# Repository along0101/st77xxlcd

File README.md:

# st77xxlcd

st77xxlcd connector

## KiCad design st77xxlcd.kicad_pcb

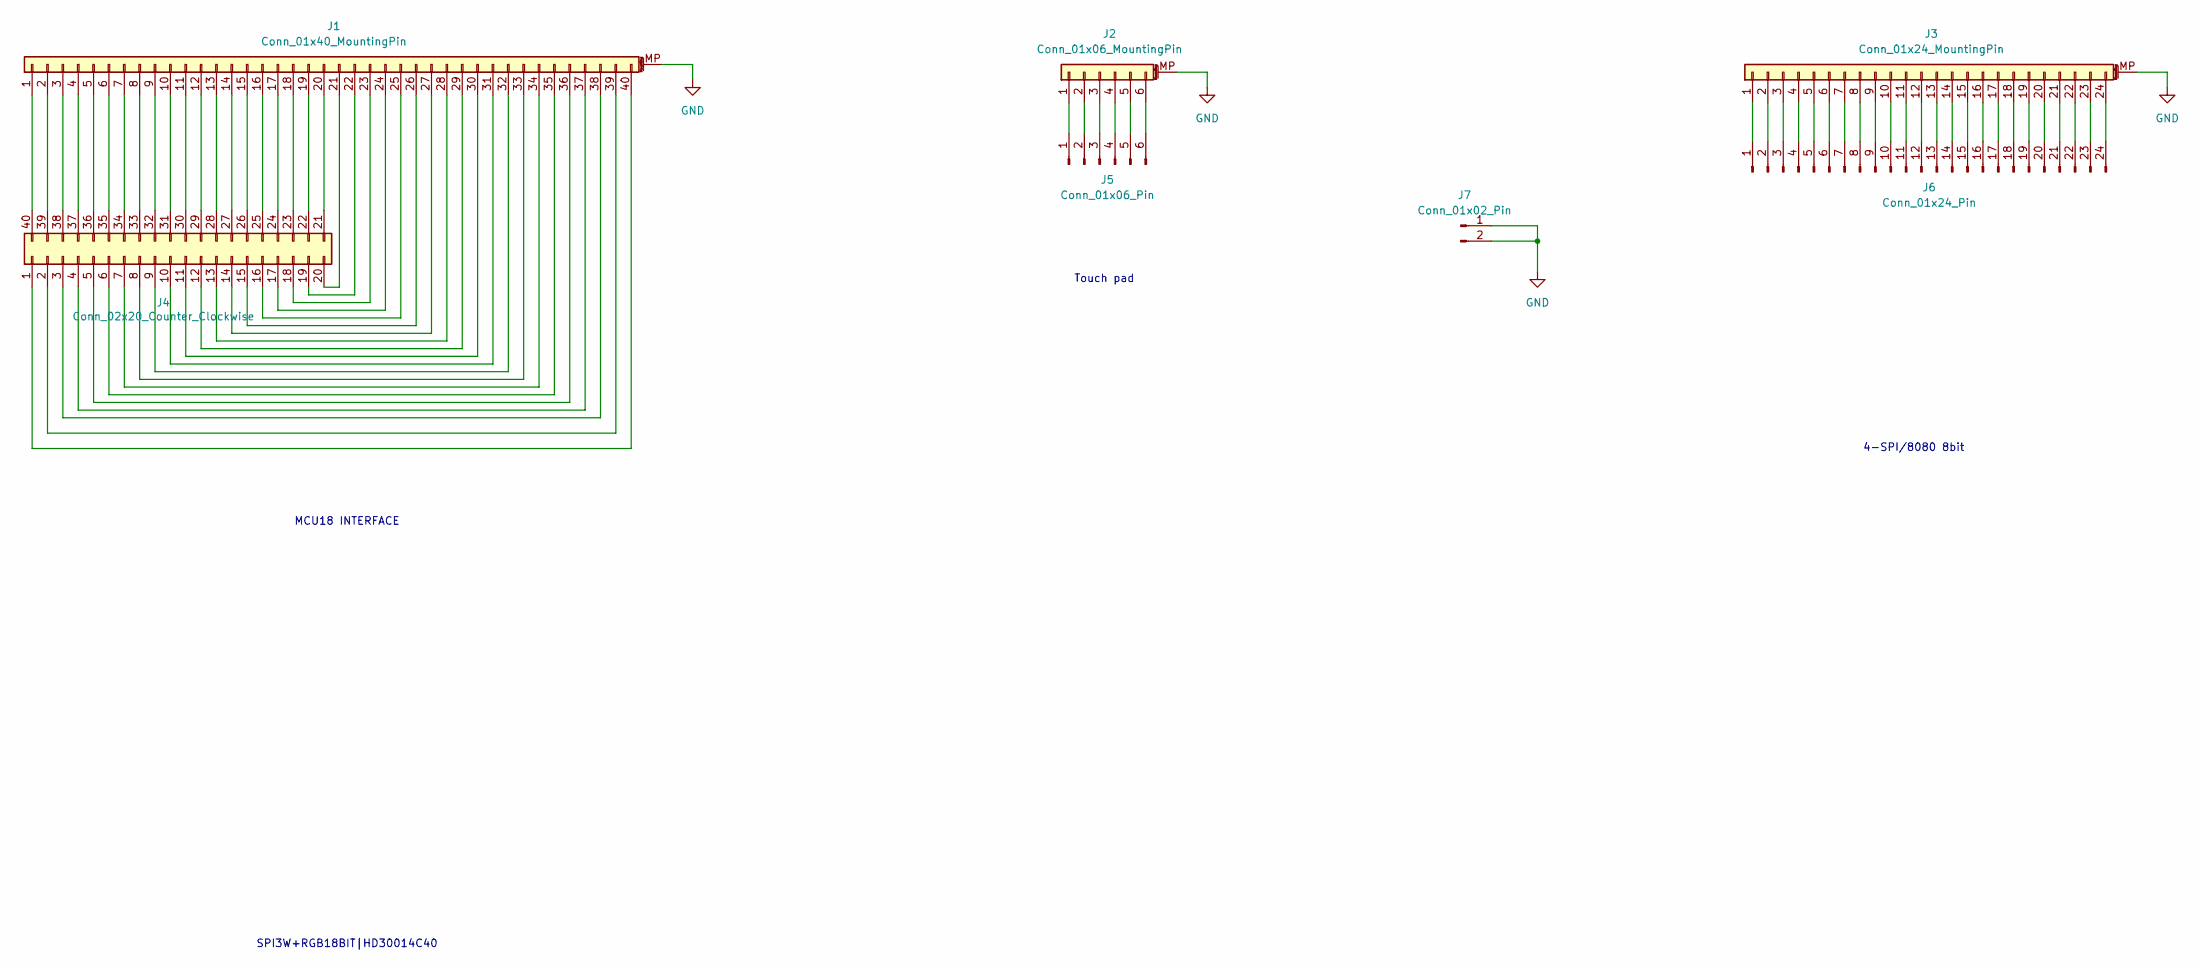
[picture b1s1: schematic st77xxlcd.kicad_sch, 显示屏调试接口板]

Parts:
J1: Conn_01x40_MountingPin; Hirose_FH12-40S-0.5SH_1x40-1MP_P0.50mm_Horizontal
J2: Conn_01x06_MountingPin; Hirose_FH12-6S-0.5SH_1x06-1MP_P0.50mm_Horizontal
J3: Conn_01x24_MountingPin; Hirose_FH12-24S-0.5SH_1x24-1MP_P0.50mm_Horizontal
J4: Conn_02x20_Counter_Clockwise; PinHeader_2x20_P2.54mm_Vertical
J5: Conn_01x06_Pin; PinHeader_1x06_P2.54mm_Vertical
J6: Conn_01x24_Pin; PinHeader_1x24_P2.54mm_Vertical
J7: Conn_01x02_Pin; PinHeader_1x02_P2.54mm_Vertical

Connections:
GND: J1.MP (MountPin), J2.MP (MountPin), J3.MP (MountPin), J7.1, J7.2
unnamed: J1.1, J4.40
unnamed: J1.2, J4.39
unnamed: J1.3, J4.38
unnamed: J1.4, J4.37
unnamed: J1.5, J4.36
unnamed: J1.6, J4.35
unnamed: J1.7, J4.34
unnamed: J1.8, J4.33
unnamed: J1.9, J4.32
unnamed: J1.10, J4.31
unnamed: J1.11, J4.30
unnamed: J1.12, J4.29
unnamed: J1.13, J4.28
unnamed: J1.14, J4.27
unnamed: J1.15, J4.26
unnamed: J1.16, J4.25
unnamed: J1.17, J4.24
unnamed: J1.18, J4.23
unnamed: J1.19, J4.22
unnamed: J1.20, J4.21
unnamed: J1.21, J4.20
unnamed: J1.22, J4.19
unnamed: J1.23, J4.18
unnamed: J1.24, J4.17
unnamed: J1.25, J4.16
unnamed: J1.26, J4.15
unnamed: J1.27, J4.14
unnamed: J1.28, J4.13
unnamed: J1.29, J4.12
unnamed: J1.30, J4.11
unnamed: J1.31, J4.10
unnamed: J1.32, J4.9
unnamed: J1.33, J4.8
unnamed: J1.34, J4.7
unnamed: J1.35, J4.6
unnamed: J1.36, J4.5
unnamed: J1.37, J4.4
unnamed: J1.38, J4.3
unnamed: J1.39, J4.2
unnamed: J1.40, J4.1
unnamed: J2.1, J5.1
unnamed: J2.2, J5.2
unnamed: J2.3, J5.3
unnamed: J2.4, J5.4
unnamed: J2.5, J5.5
unnamed: J2.6, J5.6
unnamed: J3.1, J6.1
unnamed: J3.2, J6.2
unnamed: J3.3, J6.3
unnamed: J3.4, J6.4
unnamed: J3.5, J6.5
unnamed: J3.6, J6.6
unnamed: J3.7, J6.7
unnamed: J3.8, J6.8
unnamed: J3.9, J6.9
unnamed: J3.10, J6.10
unnamed: J3.11, J6.11
unnamed: J3.12, J6.12
unnamed: J3.13, J6.13
unnamed: J3.14, J6.14
unnamed: J3.15, J6.15
unnamed: J3.16, J6.16
unnamed: J3.17, J6.17
unnamed: J3.18, J6.18
unnamed: J3.19, J6.19
unnamed: J3.20, J6.20
unnamed: J3.21, J6.21
unnamed: J3.22, J6.22
unnamed: J3.23, J6.23
unnamed: J3.24, J6.24

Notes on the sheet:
4-SPI/8080 8bit
MCU18 INTERFACE
SPI3W+RGB18BIT|HD30014C40
Touch pad

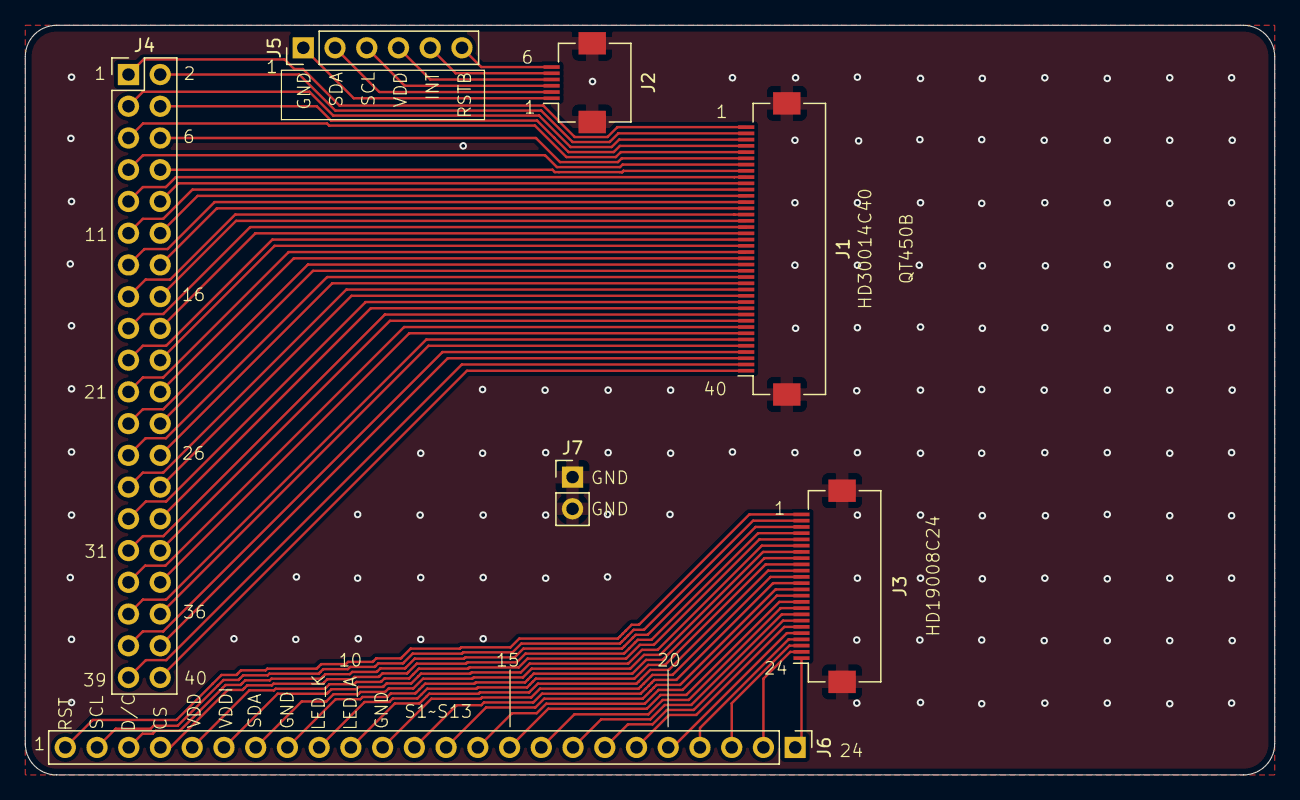
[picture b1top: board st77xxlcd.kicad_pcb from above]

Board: 2 copper layers, 100.0 x 60.0 mm, 7 parts (0 on the bottom side), 71 nets.

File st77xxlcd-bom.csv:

"编号";"位号";"封装";"数量";"名称";"供应商编号";
1;"J7";"PinHeader_1x02_P2.54mm_Vertical";1;"Conn_01x02_Pin";;;
2;"J1";"Hirose_FH12-40S-0.5SH_1x40-1MP_P0.50mm_Horizontal";1;"Conn_01x40_MountingPin";;;
3;"J6";"PinHeader_1x24_P2.54mm_Vertical";1;"Conn_01x24_Pin";;;
4;"J3";"Hirose_FH12-24S-0.5SH_1x24-1MP_P0.50mm_Horizontal";1;"Conn_01x24_MountingPin";;;
5;"J2";"Hirose_FH12-6S-0.5SH_1x06-1MP_P0.50mm_Horizontal";1;"Conn_01x06_MountingPin";;;
6;"J4";"PinHeader_2x20_P2.54mm_Vertical";1;"Conn_02x20_Counter_Clockwise";;;
7;"J5";"PinHeader_1x06_P2.54mm_Vertical";1;"Conn_01x06_Pin";;;

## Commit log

2025-03-27 [IMP] 布线
2025-03-28 [IMP] 完成布线，导出制造文件
